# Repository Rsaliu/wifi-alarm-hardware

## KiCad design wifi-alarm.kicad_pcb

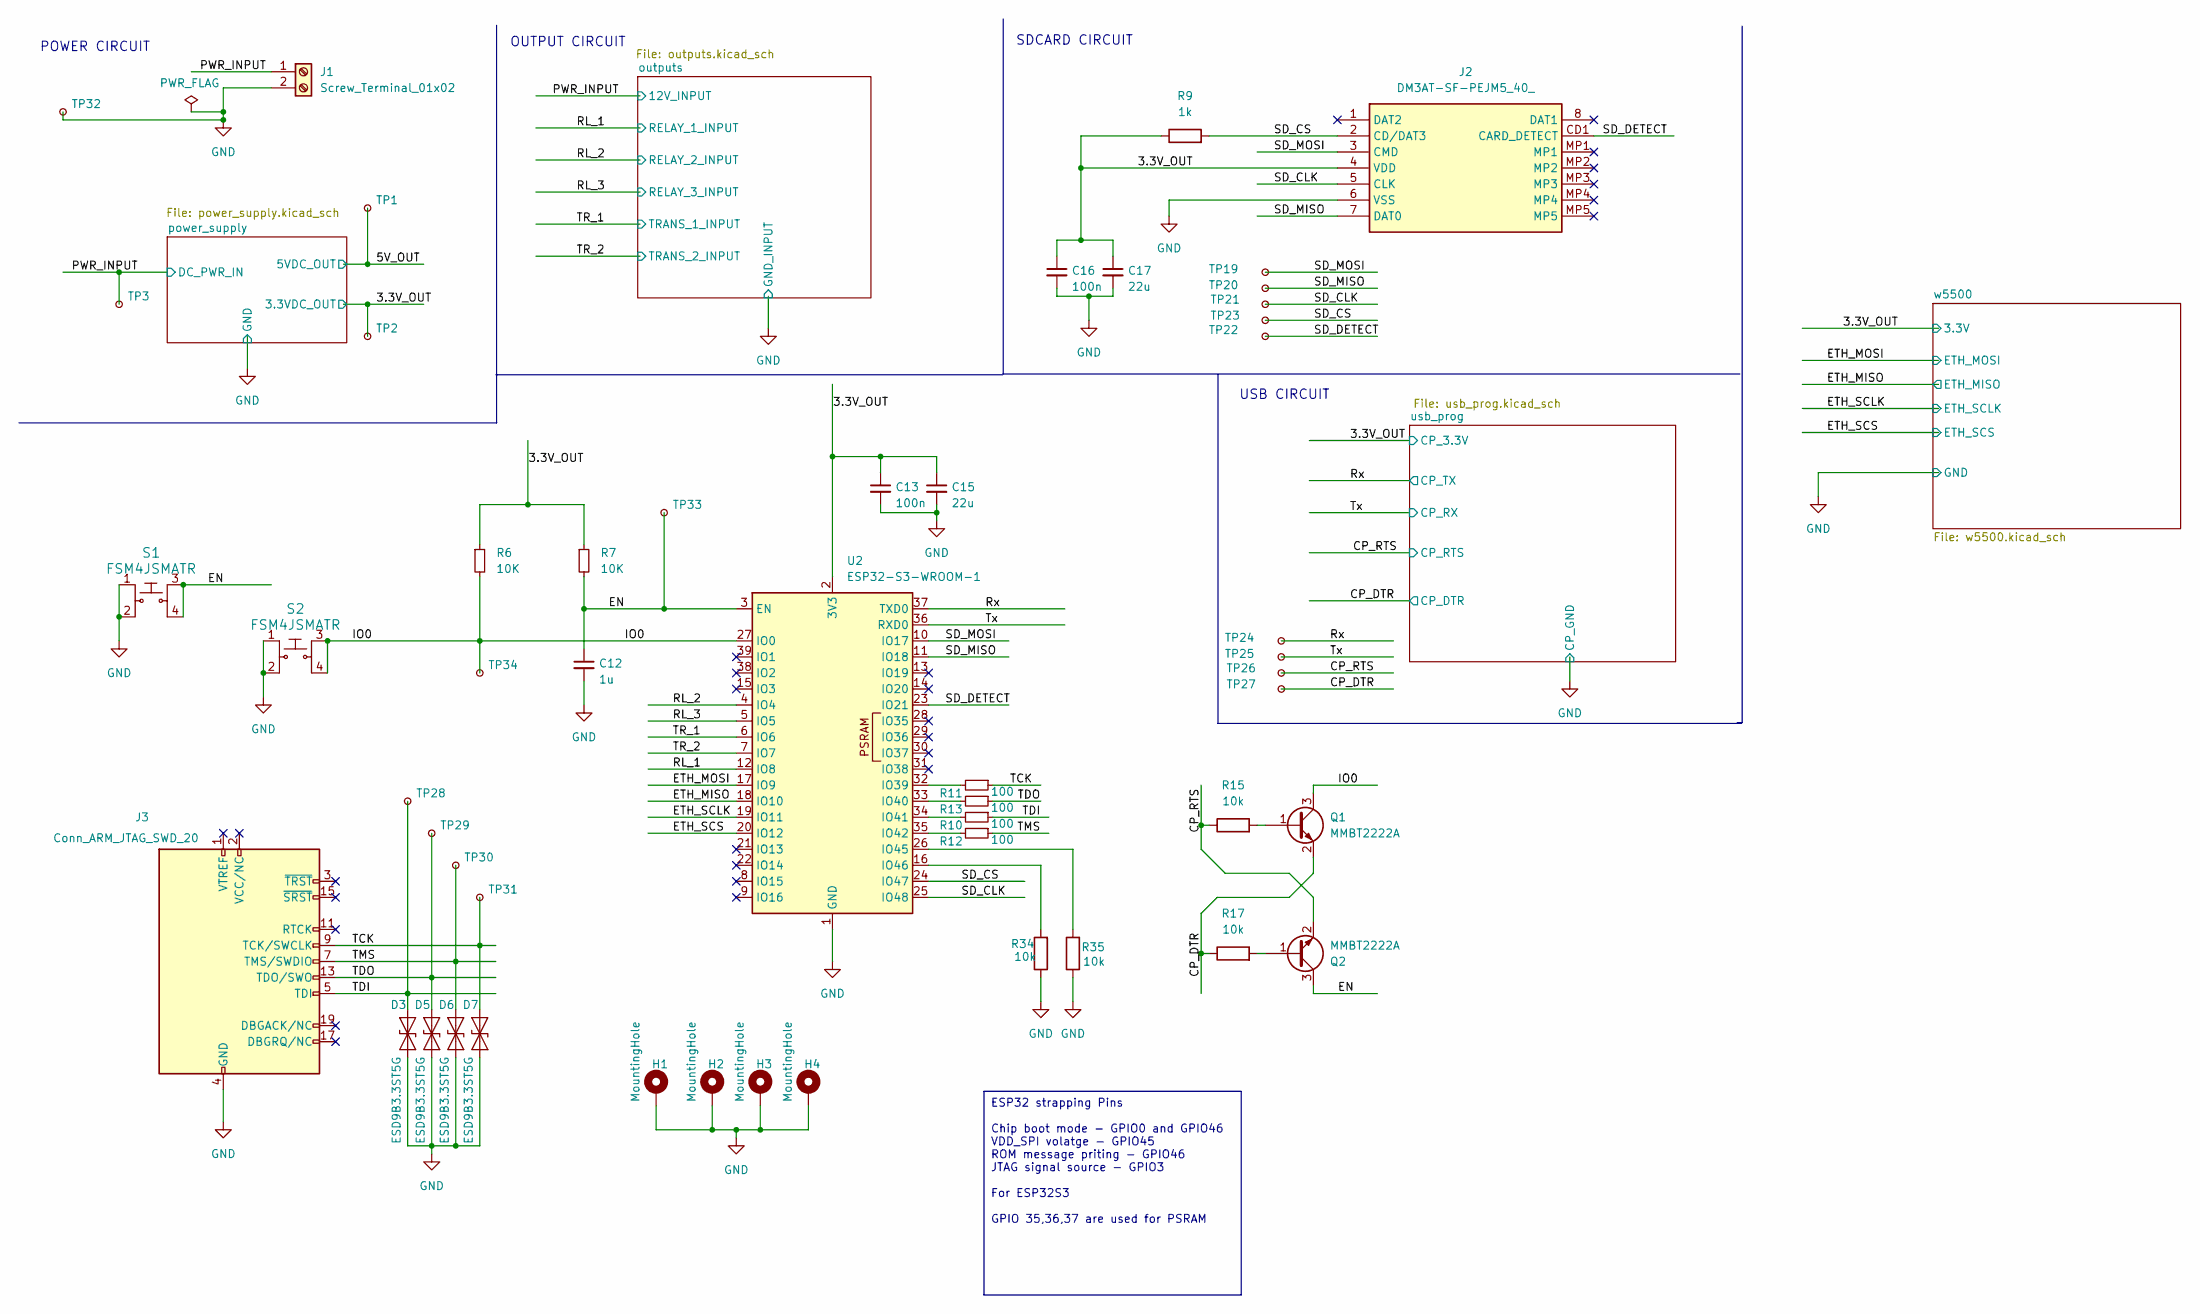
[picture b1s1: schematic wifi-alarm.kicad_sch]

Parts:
C12: 1u; C_0603_1608Metric_Pad1.08x0.95mm_HandSolder; part number CC0603KRX5R6BB105; JLCPCB Part # C106214
C13, C16: 100n; C_0603_1608Metric_Pad1.08x0.95mm_HandSolder; part number C0603C104K5RACAUTO; JLCPCB Part # C129621
C15, C17: 22u; C_1206_3216Metric_Pad1.33x1.80mm_HandSolder; part number HGC1206R5226M350NSPJ; JLCPCB Part # C22367834
D3, D5, D6, D7: ESD9B3.3ST5G; D_SOD-923; part number ESD9B3.3ST5G; JLCPCB Part # C3040608
H1, H2, H3, H4: MountingHole; MountingHole_2.5mm_Pad
J1: Screw_Terminal_01x02; TerminalBlock_bornier-2_P5.08mm
J2: DM3AT-SF-PEJM5_40_; DM3ATSFPEJM540; Mouser Part Number 798-DM3AT-SF-PEJM540
J3: Conn_ARM_JTAG_SWD_20; IDC-Header_2x10_P2.54mm_Vertical
Q1, Q2: MMBT2222A; SOT-23; part number MMBT2222A; JLCPCB Part # C83939
R6, R7: 10K; R_0603_1608Metric_Pad0.98x0.95mm_HandSolder; part number RC0603FR-0710KL; JLCPCB Part # C98220
R9: 1k; R_0603_1608Metric_Pad0.98x0.95mm_HandSolder; part number RC0603FR-071KL; JLCPCB Part # C22548
R10, R11, R12, R13: 100; R_0603_1608Metric_Pad0.98x0.95mm_HandSolder; part number RC0603FR-07100RL; JLCPCB Part # C105588
R15, R17, R34, R35: 10k; R_0603_1608Metric_Pad0.98x0.95mm_HandSolder; part number RC0603FR-0710KL; JLCPCB Part # C98220
S1, S2: FSM4JSMATR; Switch_Tactile_SMD_6x6mm; MPN FSM4JSMATR; JLCPCB Part # C178262
TP1, TP2, TP3, TP19, TP20, TP21, TP22, TP23, TP24, TP25, TP26, TP27, TP28, TP29, TP30, TP31, TP32, TP33, TP34: TestPoint_Pad_1.5x1.5mm
U2: ESP32-S3-WROOM-1; part number ESP32-S3-WROOM-1-N8R8; JLCPCB Part # C2913201

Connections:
/3.3V_OUT: C13.1, C15.1, C16.1, C17.1, J2.4 (VDD), R6.1, R7.1, R9.1, TP2.1, U2.2 (3V3); also elsewhere on the board
/5V_OUT: TP1.1; also elsewhere on the board
/CP_DTR: Q1.2 (E), R17.1, TP27.1; also elsewhere on the board
/CP_RTS: Q2.2 (E), R15.1, TP26.1; also elsewhere on the board
/EN: C12.1, Q2.3 (C), R7.2, S1.3, S1.4, TP33.1, U2.3 (EN)
/ETH_MISO: U2.18 (IO10); also elsewhere on the board
/ETH_MOSI: U2.17 (IO9); also elsewhere on the board
/ETH_SCLK: U2.19 (IO11); also elsewhere on the board
/ETH_SCS: U2.20 (IO12); also elsewhere on the board
/IO0: Q1.3 (C), R6.2, S2.3, S2.4, TP34.1, U2.27 (IO0)
/PWR_INPUT: J1.1, TP3.1; also elsewhere on the board
/RL_1: U2.12 (IO8); also elsewhere on the board
/RL_2: U2.4 (IO4); also elsewhere on the board
/RL_3: U2.5 (IO5); also elsewhere on the board
/Rx: TP24.1, U2.37 (TXD0); also elsewhere on the board
/SD_CLK: J2.5 (CLK), TP21.1, U2.25 (IO48)
/SD_CS: J2.2 (CD/DAT3), R9.2, TP23.1, U2.24 (IO47)
/SD_DETECT: J2.CD1 (CARD_DETECT), TP22.1, U2.23 (IO21)
/SD_MISO: J2.7 (DAT0), TP20.1, U2.11 (IO18)
/SD_MOSI: J2.3 (CMD), TP19.1, U2.10 (IO17)
/TCK: D7.2 (A2), J3.9 (TCK/SWCLK), R11.1, TP31.1
/TDI: D3.2 (A2), J3.5 (TDI), R10.1, TP28.1
/TDO: D5.2 (A2), J3.13 (TDO/SWO), R13.1, TP29.1
/TMS: D6.2 (A2), J3.7 (TMS/SWDIO), R12.1, TP30.1
/TR_1: U2.6 (IO6); also elsewhere on the board
/TR_2: U2.7 (IO7); also elsewhere on the board
/Tx: TP25.1, U2.36 (RXD0); also elsewhere on the board
GND: C12.2, C13.2, C15.2, C16.2, C17.2, D3.1 (A1), D5.1 (A1), D6.1 (A1), D7.1 (A1), H1.1, H2.1, H3.1, H4.1, J1.2, J2.6 (VSS), J3.4 (GND), J3.6 (GND), J3.8 (GND), J3.10 (GND), J3.12 (GND), J3.14 (GND), J3.16 (GND), J3.18 (GND), J3.20 (GND), R34.1, R35.1, S1.1, S1.2, S2.1, S2.2, TP32.1, U2.1 (GND), U2.40 (GND), U2.41 (GND); also elsewhere on the board
unnamed: Q1.1 (B), R15.2
unnamed: Q2.1 (B), R17.2
unnamed: R11.2, U2.32 (IO39)
unnamed: R13.2, U2.33 (IO40)
unnamed: R10.2, U2.34 (IO41)
unnamed: R12.2, U2.35 (IO42)
unnamed: R35.2, U2.26 (IO45)
unnamed: R34.2, U2.16 (IO46)

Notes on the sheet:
ESP32 strapping Pins Chip boot mode - GPIO0 and GPIO46 VDD_SPI volatge - GPIO45 ROM message priting - GPIO46 JTAG signal source - GPIO3 For ESP32S3 GPIO 35,36,37 are used for PSRAM
SDCARD CIRCUIT
USB CIRCUIT
OUTPUT CIRCUIT
POWER CIRCUIT

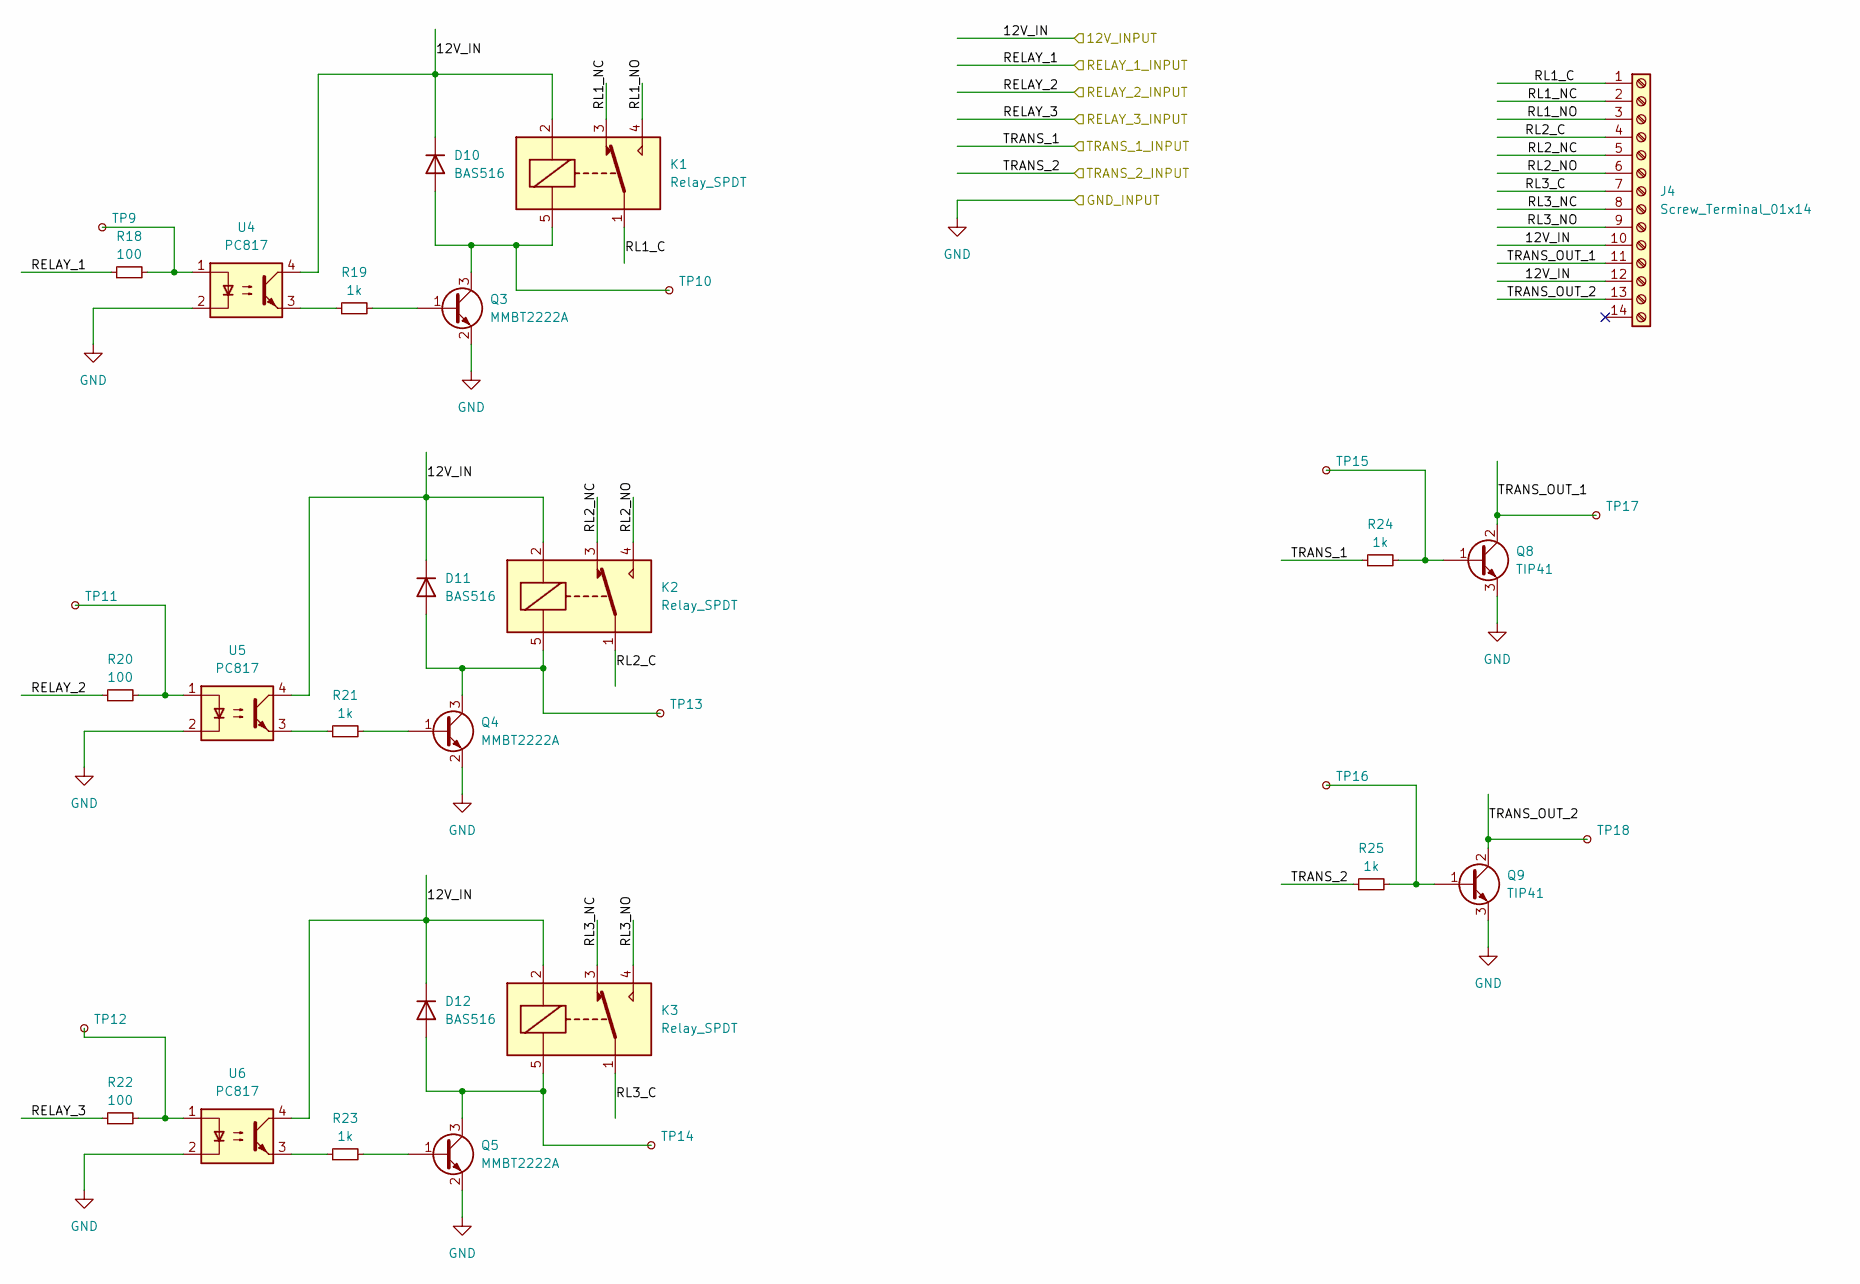
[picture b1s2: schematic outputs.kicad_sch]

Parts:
D10, D11, D12: BAS516; D_SOD-523; part number BAS516; JLCPCB Part # C5178954
J4: Screw_Terminal_01x14; TerminalBlock_Xinya_XY308-2.54-14P_1x14_P2.54mm_Horizontal
K1, K2, K3: Relay_SPDT; Relay_SPDT_Omron-G5LE-1; part number G5LE-1-DC12
Q3, Q4, Q5: MMBT2222A; SOT-23; part number MMBT2222A; JLCPCB Part # C83939
Q8, Q9: TIP41; TO-220-3_Vertical; part number TIP41; JLCPCB Part # C963394
R18, R20, R22: 100; R_0603_1608Metric_Pad0.98x0.95mm_HandSolder; part number RC0603FR-07100RL; JLCPCB Part # C105588
R19, R21, R23, R24, R25: 1k; R_0603_1608Metric_Pad0.98x0.95mm_HandSolder; part number RC0603FR-071KL; JLCPCB Part # C22548
TP9, TP10, TP11, TP12, TP13, TP14, TP15, TP16, TP17, TP18: TestPoint_Pad_1.5x1.5mm
U4, U5, U6: PC817; DIP-4_W7.62mm; part number PC817B; JLCPCB Part # C5451664

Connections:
/PWR_INPUT: D10.1 (K), D11.1 (K), D12.1 (K), J4.10, J4.12, K1.2, K2.2, K3.2, U4.4, U5.4, U6.4; also elsewhere on the board
/RL_1: R18.1; also elsewhere on the board
/RL_2: R20.1; also elsewhere on the board
/RL_3: R22.1; also elsewhere on the board
/TR_1: R24.1; also elsewhere on the board
/TR_2: R25.1; also elsewhere on the board
/outputs/RL1_C: J4.1, K1.1
/outputs/RL1_NC: J4.2, K1.3
/outputs/RL1_NO: J4.3, K1.4
/outputs/RL2_C: J4.4, K2.1
/outputs/RL2_NC: J4.5, K2.3
/outputs/RL2_NO: J4.6, K2.4
/outputs/RL3_C: J4.7, K3.1
/outputs/RL3_NC: J4.8, K3.3
/outputs/RL3_NO: J4.9, K3.4
/outputs/TRANS_OUT_1: J4.11, Q8.2 (C), TP17.1
/outputs/TRANS_OUT_2: J4.13, Q9.2 (C), TP18.1
GND: Q3.2 (E), Q4.2 (E), Q5.2 (E), Q8.3 (E), Q9.3 (E), U4.2, U5.2, U6.2; also elsewhere on the board
unnamed: D10.2 (A), K1.5, Q3.3 (C), TP10.1
unnamed: D11.2 (A), K2.5, Q4.3 (C), TP13.1
unnamed: D12.2 (A), K3.5, Q5.3 (C), TP14.1
unnamed: Q3.1 (B), R19.2
unnamed: Q4.1 (B), R21.2
unnamed: Q5.1 (B), R23.2
unnamed: Q8.1 (B), R24.2, TP15.1
unnamed: Q9.1 (B), R25.2, TP16.1
unnamed: R18.2, TP9.1, U4.1
unnamed: R19.1, U4.3
unnamed: R20.2, TP11.1, U5.1
unnamed: R21.1, U5.3
unnamed: R22.2, TP12.1, U6.1
unnamed: R23.1, U6.3

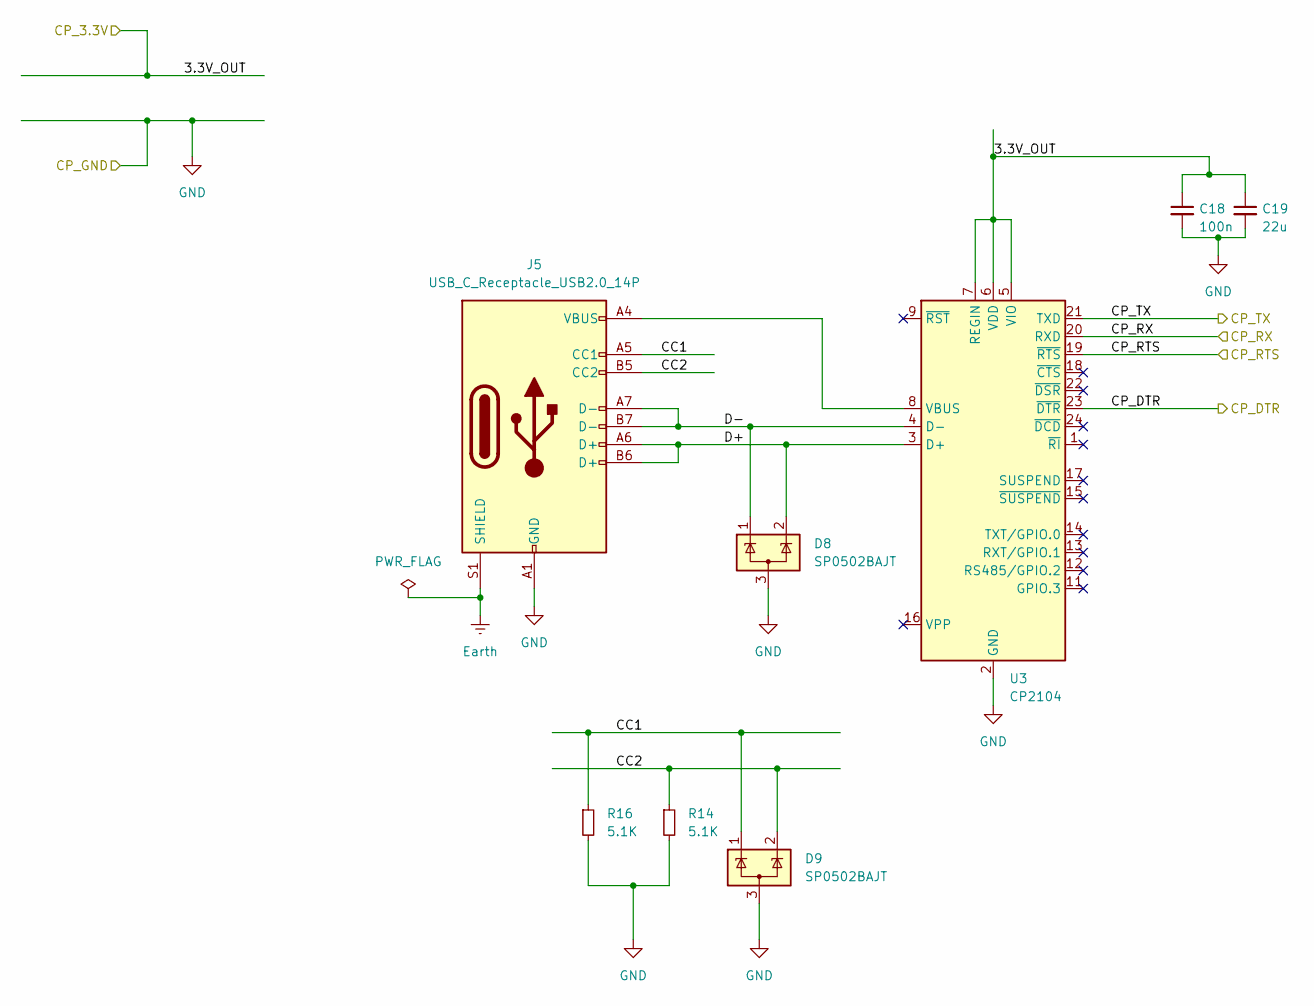
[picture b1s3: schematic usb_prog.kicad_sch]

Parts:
C18: 100n; C_0603_1608Metric_Pad1.08x0.95mm_HandSolder; part number C0603C104K5RACAUTO; JLCPCB Part # C129621
C19: 22u; C_1206_3216Metric_Pad1.33x1.80mm_HandSolder; part number HGC1206R5226M350NSPJ; JLCPCB Part # C22367834
D8, D9: SP0502BAJT; SOT-323_SC-70; part number SP0502BAJTG; JLCPCB Part # C207262
J5: USB_C_Receptacle_USB2.0_14P; USB_C_Receptacle_HCTL_HC-TYPE-C-16P-01A; part number TYPE C-CQ-110PWB; JLCPCB Part # C2936200
R14, R16: 5.1K; R_0603_1608Metric_Pad0.98x0.95mm_HandSolder; part number RC0603FR-075K1L; JLCPCB Part # C105580
U3: CP2104; QFN-24-1EP_4x4mm_P0.5mm_EP2.6x2.6mm; part number CP2104-F03-GM; JLCPCB Part # C47742

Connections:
/3.3V_OUT: C18.1, C19.1, U3.5 (VIO), U3.6 (VDD), U3.7 (REGIN); also elsewhere on the board
/CP_DTR: U3.23 (~DTR); also elsewhere on the board
/CP_RTS: U3.19 (~RTS); also elsewhere on the board
/Rx: U3.21 (TXD); also elsewhere on the board
/Tx: U3.20 (RXD); also elsewhere on the board
/usb_prog/CC1: D9.1 (K), J5.A5 (CC1), R16.1
/usb_prog/CC2: D9.2 (K), J5.B5 (CC2), R14.1
/usb_prog/D+: D8.2 (K), J5.A6 (D+), J5.B6 (D+), U3.3 (D+)
/usb_prog/D-: D8.1 (K), J5.A7 (D-), J5.B7 (D-), U3.4 (D-)
Earth: J5.S1 (SHIELD); also elsewhere on the board
GND: C18.2, C19.2, D8.3 (A), D9.3 (A), J5.A1 (GND), J5.A12 (GND), J5.B1 (GND), J5.B12 (GND), R14.2, R16.2, U3.2 (GND), U3.25 (GND); also elsewhere on the board
unnamed: J5.A4 (VBUS), J5.A9 (VBUS), J5.B4 (VBUS), J5.B9 (VBUS), U3.8 (VBUS)

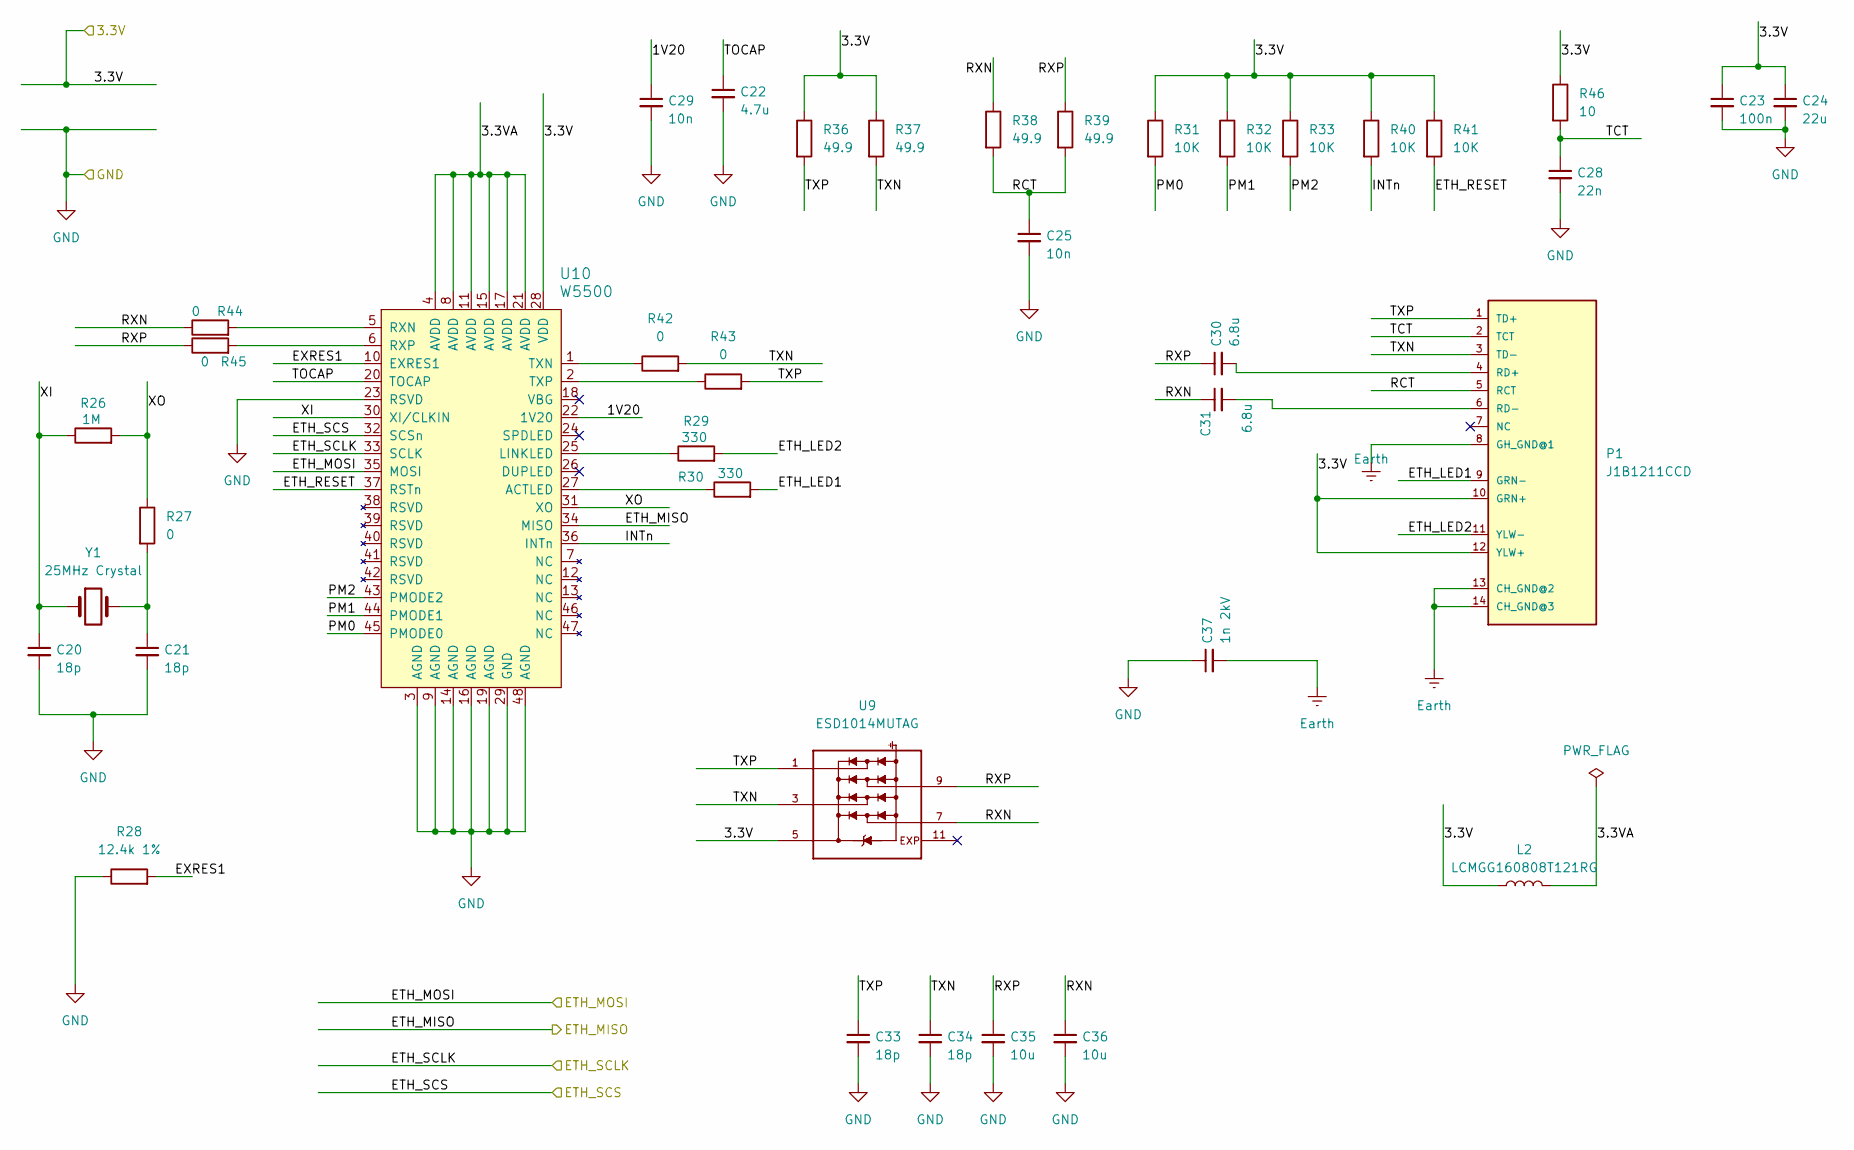
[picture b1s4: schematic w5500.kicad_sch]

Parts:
C20, C21, C33, C34: 18p; C_0603_1608Metric_Pad1.08x0.95mm_HandSolder; part number CC0603JRNPO8BN180; JLCPCB Part # C519389
C22: 4.7u; C_1206_3216Metric_Pad1.33x1.80mm_HandSolder; part number 0603X475K250; JLCPCB Part # C152896
C23: 100n; C_0603_1608Metric_Pad1.08x0.95mm_HandSolder; part number C0603C104K5RACAUTO; JLCPCB Part # C129621
C24: 22u; C_1206_3216Metric_Pad1.33x1.80mm_HandSolder; part number HGC1206R5226M350NSPJ; JLCPCB Part # C22367834
C25, C29: 10n; C_0603_1608Metric_Pad1.08x0.95mm_HandSolder; part number CT41G-0603-2X1-50V-0.01μF-K(N); JLCPCB Part # C136131
C28: 22n; C_1206_3216Metric_Pad1.33x1.80mm_HandSolder; part number 1206B106K500NT; JLCPCB Part # C303950
C30, C31: 6.8u; C_1206_3216Metric_Pad1.33x1.80mm_HandSolder; part number 1206B106K500NT; JLCPCB Part # C303950
C35, C36: 10u; C_1206_3216Metric_Pad1.33x1.80mm_HandSolder; part number 1206B106K500NT; JLCPCB Part # C303950
C37: 1n 2kV; C_0603_1608Metric_Pad1.08x0.95mm_HandSolder; part number CC0603KRX7R8BB102; JLCPCB Part # C519404
L2: LCMGG160808T121RG; R_0603_1608Metric_Pad0.98x0.95mm_HandSolder; part number LCMGG160808T121RG; JLCPCB Part # C6286234
P1: J1B1211CCD; part number J1B1211CCD; JLCPCB Part # C910371
R26: 1M; R_0603_1608Metric_Pad0.98x0.95mm_HandSolder; part number RC0603FR-071ML; JLCPCB Part # C105578
R27, R42, R43, R44, R45: 0; R_0603_1608Metric_Pad0.98x0.95mm_HandSolder; part number RC0603JR-070RL; JLCPCB Part # C95177
R28: 12.4k 1%; R_0603_1608Metric_Pad0.98x0.95mm_HandSolder; part number RC0603FR-0712K4L; JLCPCB Part # C137798
R29, R30: 330; R_0603_1608Metric_Pad0.98x0.95mm_HandSolder; part number RC0603FR-07330RL; JLCPCB Part # C105881
R31, R32, R33, R40, R41: 10K; R_0603_1608Metric_Pad0.98x0.95mm_HandSolder; part number RC0603FR-0710KL; JLCPCB Part # C98220
R36, R37, R38, R39: 49.9; R_0603_1608Metric_Pad0.98x0.95mm_HandSolder; part number RC0603FR-0749R9L; JLCPCB Part # C114625
R46: 10; R_0603_1608Metric_Pad0.98x0.95mm_HandSolder; part number RC0603FR-0749R9L; JLCPCB Part # C114625
U9: ESD1014MUTAG; SON50P260X260X55-11N; PARTREV 7; JLCPCB Part # C463928
U10: W5500; LQFP-48_7x7mm; MPN W5500; JLCPCB Part # C32843
Y1: 25MHz Crystal; Crystal_SMD_5032-2Pin_5.0x3.2mm_HandSoldering; part number 5032 25M 20PF 20PPM 2P; JLCPCB Part # C5380317

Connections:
/3.3V_OUT: C23.1, C24.1, L2.1, P1.10 (GRN+), P1.12 (YLW+), R31.1, R32.1, R33.1, R36.1, R37.1, R40.1, R41.1, R46.1, U9.5, U10.28 (VDD); also elsewhere on the board
/ETH_MISO: U10.34 (MISO); also elsewhere on the board
/ETH_MOSI: U10.35 (MOSI); also elsewhere on the board
/ETH_SCLK: U10.33 (SCLK); also elsewhere on the board
/ETH_SCS: U10.32 (SCSn); also elsewhere on the board
/w5500/1V20: C29.1, U10.22 (1V20)
/w5500/3.3VA: L2.2, U10.4 (AVDD), U10.8 (AVDD), U10.11 (AVDD), U10.15 (AVDD), U10.17 (AVDD), U10.21 (AVDD)
/w5500/ETH_LED1: P1.9 (GRN-), R30.2
/w5500/ETH_LED2: P1.11 (YLW-), R29.2
/w5500/ETH_RESET: R41.2, U10.37 (RSTn)
/w5500/EXRES1: R28.2, U10.10 (EXRES1)
/w5500/INTn: R40.2, U10.36 (INTn)
/w5500/PM0: R31.2, U10.45 (PMODE0)
/w5500/PM1: R32.2, U10.44 (PMODE1)
/w5500/PM2: R33.2, U10.43 (PMODE2)
/w5500/RCT: C25.1, P1.5 (RCT), R38.2, R39.2
/w5500/RXN: C31.1, C36.1, R38.1, R44.1, U9.7
/w5500/RXP: C30.1, C35.1, R39.1, R45.1, U9.9
/w5500/TCT: C28.1, P1.2 (TCT), R46.2
/w5500/TOCAP: C22.1, U10.20 (TOCAP)
/w5500/TXN: C34.1, P1.3 (TD-), R37.2, R42.2, U9.3
/w5500/TXP: C33.1, P1.1 (TD+), R36.2, R43.2, U9.1
/w5500/XI: C20.1, R26.1, U10.30 (XI/CLKIN), Y1.1
/w5500/XO: R26.2, R27.1, U10.31 (XO)
Earth: C37.2, P1.8 (GH_GND@1), P1.13 (CH_GND@2), P1.14 (CH_GND@3); also elsewhere on the board
GND: C20.2, C21.2, C22.2, C23.2, C24.2, C25.2, C28.2, C29.2, C33.2, C34.2, C35.2, C36.2, C37.1, R28.1, U10.3 (AGND), U10.9 (AGND), U10.14 (AGND), U10.16 (AGND), U10.19 (AGND), U10.23 (RSVD), U10.29 (GND), U10.48 (AGND); also elsewhere on the board
unnamed: C21.1, R27.2, Y1.2
unnamed: C30.2, P1.4 (RD+)
unnamed: C31.2, P1.6 (RD-)
unnamed: R30.1, U10.27 (ACTLED)
unnamed: R29.1, U10.25 (LINKLED)
unnamed: R44.2, U10.5 (RXN)
unnamed: R45.2, U10.6 (RXP)
unnamed: R42.1, U10.1 (TXN)
unnamed: R43.1, U10.2 (TXP)

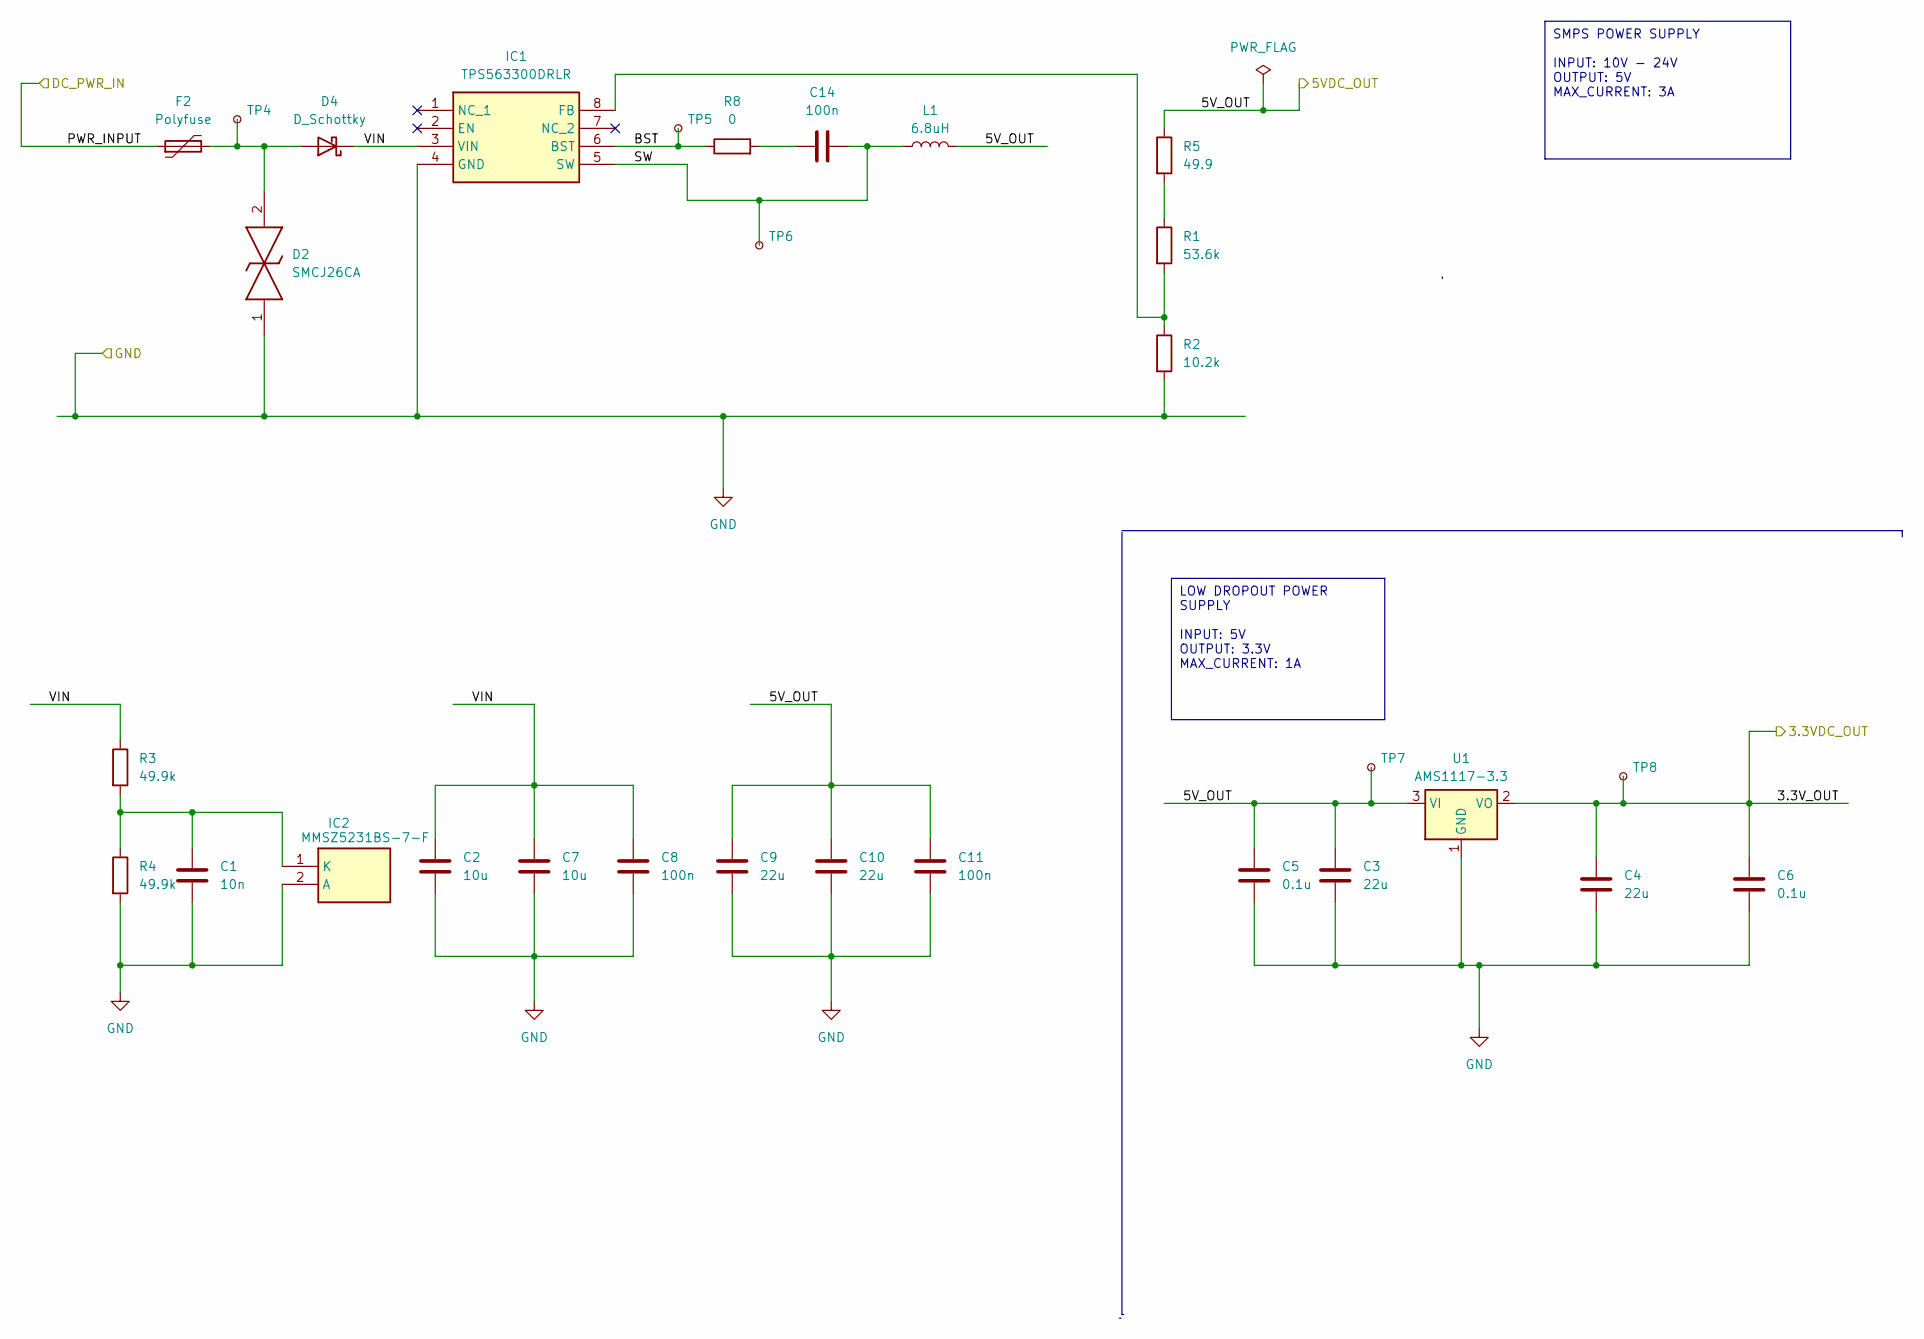
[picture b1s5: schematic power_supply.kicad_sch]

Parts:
C1: 10n; C_0603_1608Metric_Pad1.08x0.95mm_HandSolder; part number CT41G-0603-2X1-50V-0.01μF-K(N); JLCPCB Part # C136131
C2, C7: 10u; C_1206_3216Metric_Pad1.33x1.80mm_HandSolder; part number 1206B106K500NT; JLCPCB Part # C303950
C3, C4, C9, C10: 22u; C_1206_3216Metric_Pad1.33x1.80mm_HandSolder; part number HGC1206R5226M350NSPJ; JLCPCB Part # C22367834
C5, C6: 0.1u; C_0603_1608Metric_Pad1.08x0.95mm_HandSolder; part number CC0603KRX7R6BB104; JLCPCB Part # C519438
C8, C11, C14: 100n; C_0603_1608Metric_Pad1.08x0.95mm_HandSolder; part number C0603C104K5RACAUTO; JLCPCB Part # C129621
D2: SMCJ26CA; DIONM7959X262N; Mouser Part Number 576-SMCJ26CA
D4: D_Schottky; SOD2513X120N; part number MBR230LSFT1G; JLCPCB Part # C126673
F2: Polyfuse; FUSC3226X85N; part number MF-USHT050KX-2; JLCPCB Part # C3760720
IC1: TPS563300DRLR; TPS62932DRLR; Mouser Part Number 595-TPS563300DRLR
IC2: MMSZ5231BS-7-F; SOD2513X120N; Mouser Part Number 621-MMSZ5231BS-F
L1: 6.8uH; 74439346068; part number SPM10040T-6R8M; JLCPCB Part # C138682
R1: 53.6k; R_0603_1608Metric_Pad0.98x0.95mm_HandSolder; part number RC0603FR-0753K6L; JLCPCB Part # C137700
R2: 10.2k; R_0603_1608Metric_Pad0.98x0.95mm_HandSolder; part number RC0603FR-0710K2L; JLCPCB Part # C183219
R3, R4: 49.9k; R_0603_1608Metric_Pad0.98x0.95mm_HandSolder; part number RC0603FR-0749K9L; JLCPCB Part # C114624
R5: 49.9; R_0603_1608Metric_Pad0.98x0.95mm_HandSolder; part number RC0603FR-0749R9L; JLCPCB Part # C114625
R8: 0; R_0603_1608Metric_Pad0.98x0.95mm_HandSolder; part number RC0603JR-070RL; JLCPCB Part # C95177
TP4, TP5, TP6, TP7, TP8: TestPoint_Pad_1.5x1.5mm
U1: AMS1117-3.3; SOT-223-3_TabPin2; part number AMS1117-3.3; JLCPCB Part # C2992570

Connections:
/3.3V_OUT: C4.1, C6.1, TP8.1, U1.2 (VO); also elsewhere on the board
/5V_OUT: C3.1, C5.1, C9.1, C10.1, C11.1, L1.2, R5.1, TP7.1, U1.3 (VI); also elsewhere on the board
/PWR_INPUT: F2.1; also elsewhere on the board
/power_supply/BST: IC1.6 (BST), R8.1, TP5.1
/power_supply/SW: C14.2, IC1.5 (SW), L1.1, TP6.1
/power_supply/VIN: C2.1, C7.1, C8.1, D4.1 (K), IC1.3 (VIN), R3.1
GND: C1.2, C2.2, C3.2, C4.2, C5.2, C6.2, C7.2, C8.2, C9.2, C10.2, C11.2, D2.1, IC1.4 (GND), IC2.2 (A), R2.2, R4.2, U1.1 (GND); also elsewhere on the board
unnamed: C14.1, R8.2
unnamed: D2.2, D4.2 (A), F2.2, TP4.1
unnamed: IC1.8 (FB), R1.2, R2.1
unnamed: C1.1, IC2.1 (K), R3.2, R4.1
unnamed: R1.1, R5.2

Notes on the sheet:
LOW DROPOUT POWER SUPPLY INPUT: 5V OUTPUT: 3.3V MAX_CURRENT: 1A
SMPS POWER SUPPLY INPUT: 10V - 24V OUTPUT: 5V MAX_CURRENT: 3A

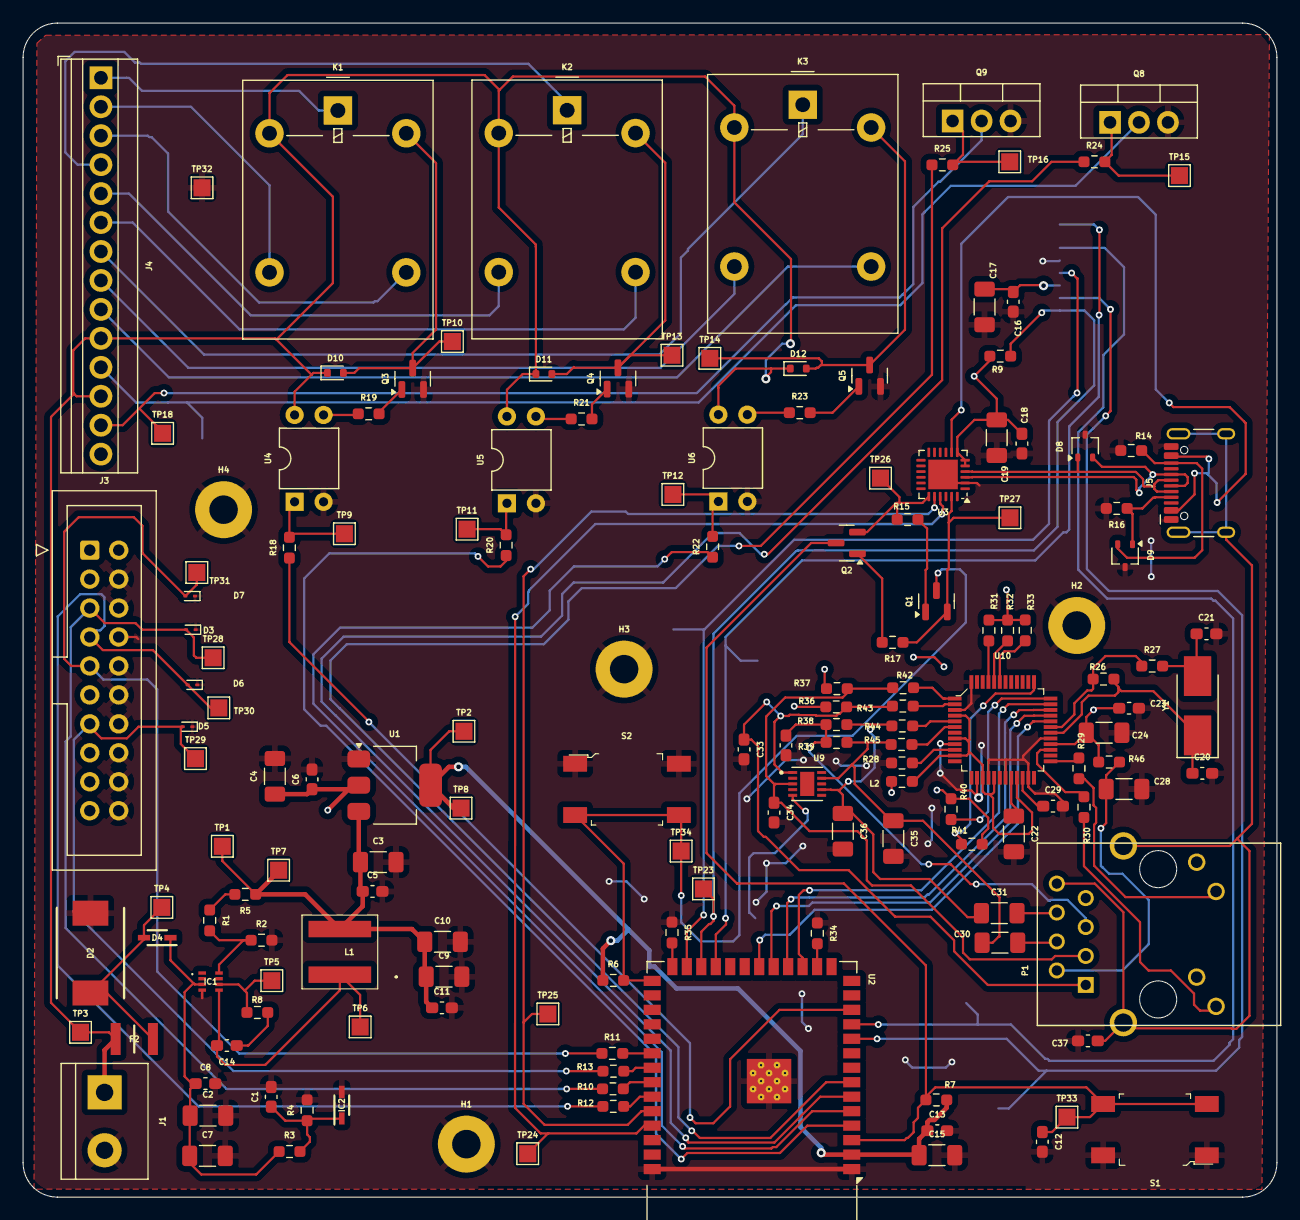
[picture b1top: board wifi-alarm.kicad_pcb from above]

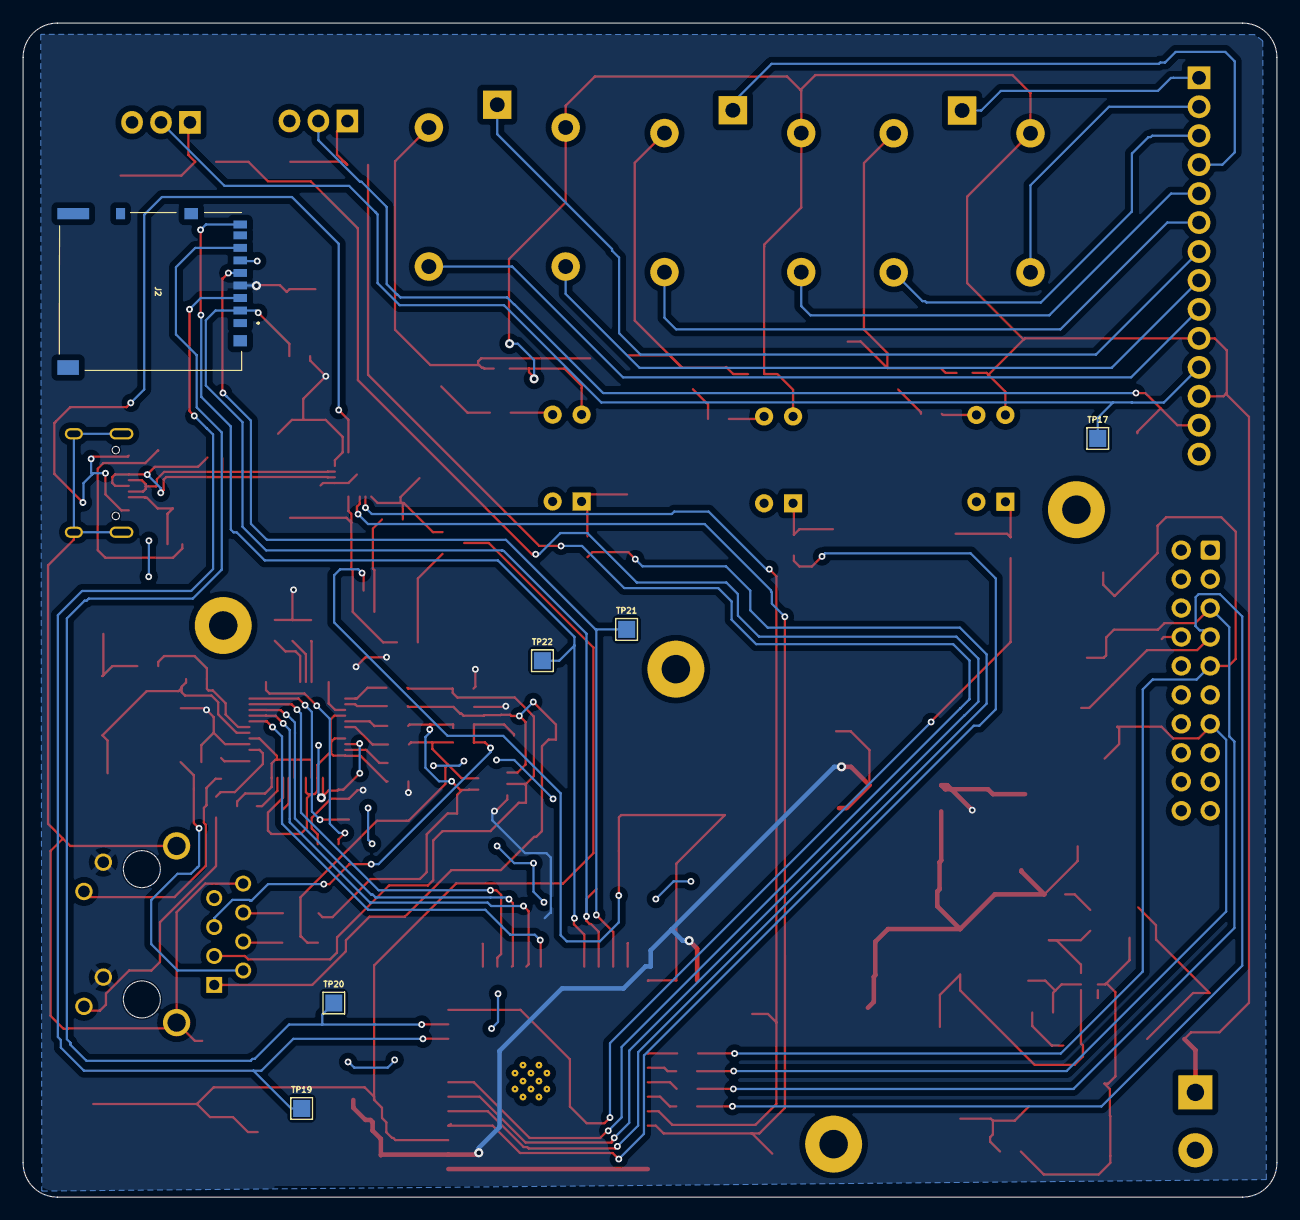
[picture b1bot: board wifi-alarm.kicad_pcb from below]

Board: 2 copper layers, 110.0 x 103.0 mm, 161 parts (6 on the bottom side), 103 nets.

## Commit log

2024-08-28 Initial power supply design with LM2596
2024-09-03 finished without LAN
2024-09-04 Correct pins in schematics and add LAN8270
2024-09-10 Add w5500 LAN to SPI because S3 does not have RMII, so we can't use LAN8720
